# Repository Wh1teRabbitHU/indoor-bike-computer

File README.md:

# indoor-bike-computer

- [indoor-bike-computer](#indoor-bike-computer)
	- [Description](#description)
	- [Sensors](#sensors)
		- [Candelance sensor](#candelance-sensor)
		- [Difficulty sensor](#difficulty-sensor)
	- [Firmware](#firmware)
	- [Images](#images)
		- [Computer 3D render, Front](#computer-3d-render-front)
		- [Computer 3D render, Back](#computer-3d-render-back)

## Description

It's a custom computer for indoor bikes to measure cadence, speed and power, store sessions, visualise ongoing statistics and replace non chargeable solutions. This project is created for the [Joroto X2 Pro](https://jorotofitness.com/products/joroto-x2pro-bluetooth-stationary-exercise-bike) indoor bike, but can be used with any other, similarly operating bikes as well!

The sensors connect to the unit the following way:

There are 2 sensor headers on the computer, one for the Candelance sensor and the other to measure the manual difficulty adjustment knob.

## Sensors

### Candelance sensor

You need to connect the following 2 pins:

- Revolution signal: This signal sends a pulse whenever the bike's crank is aligned with the sensor. The signal is triggered once every revolution and the speed is calculated based on the time difference between two pulse. For precise distance measurement, you can change the default values of the bike in the settings.
- GND: This is the shared GND line

### Difficulty sensor

You need to connect the following 3 pins:

- +3V3: This powers the sensor on the bike
- Difficulty signal: This comes from the knob, and depending on the current difficulty level, it provides a voltage between GND and +3V3 volt. (it's not a linear value and there is a starting and ending voltage level) This can be calibrated in the settings on the computer for a precise measurement.
- GND: This is the shared GND line

## Firmware

I'm using [LVGL](https://lvgl.io/) an open source embedded graphics library, to handle the UI elements for the computer. The drivers for the various chips and the bike are custom made and can be located under the `Firmware/STM32F446/Core/Inc/Drivers` and `Firmware/STM32F446/Core/Src/Drivers` folders.

List of drivers:

- ER_TFT035: Display driver. [Details](https://www.buydisplay.com/serial-spi-3-5-inch-tft-lcd-module-in-320x480-optl-touchscreen-ili9488)
- MCP3421: ADC chip from MicroChip. [Details](https://www.microchip.com/en-us/product/mcp3421)
- SD card: SD card middleware on top of the FatFS implementation, to make handling file read and write simpler

## Images

### Computer 3D render, Front

### Computer 3D render, Back

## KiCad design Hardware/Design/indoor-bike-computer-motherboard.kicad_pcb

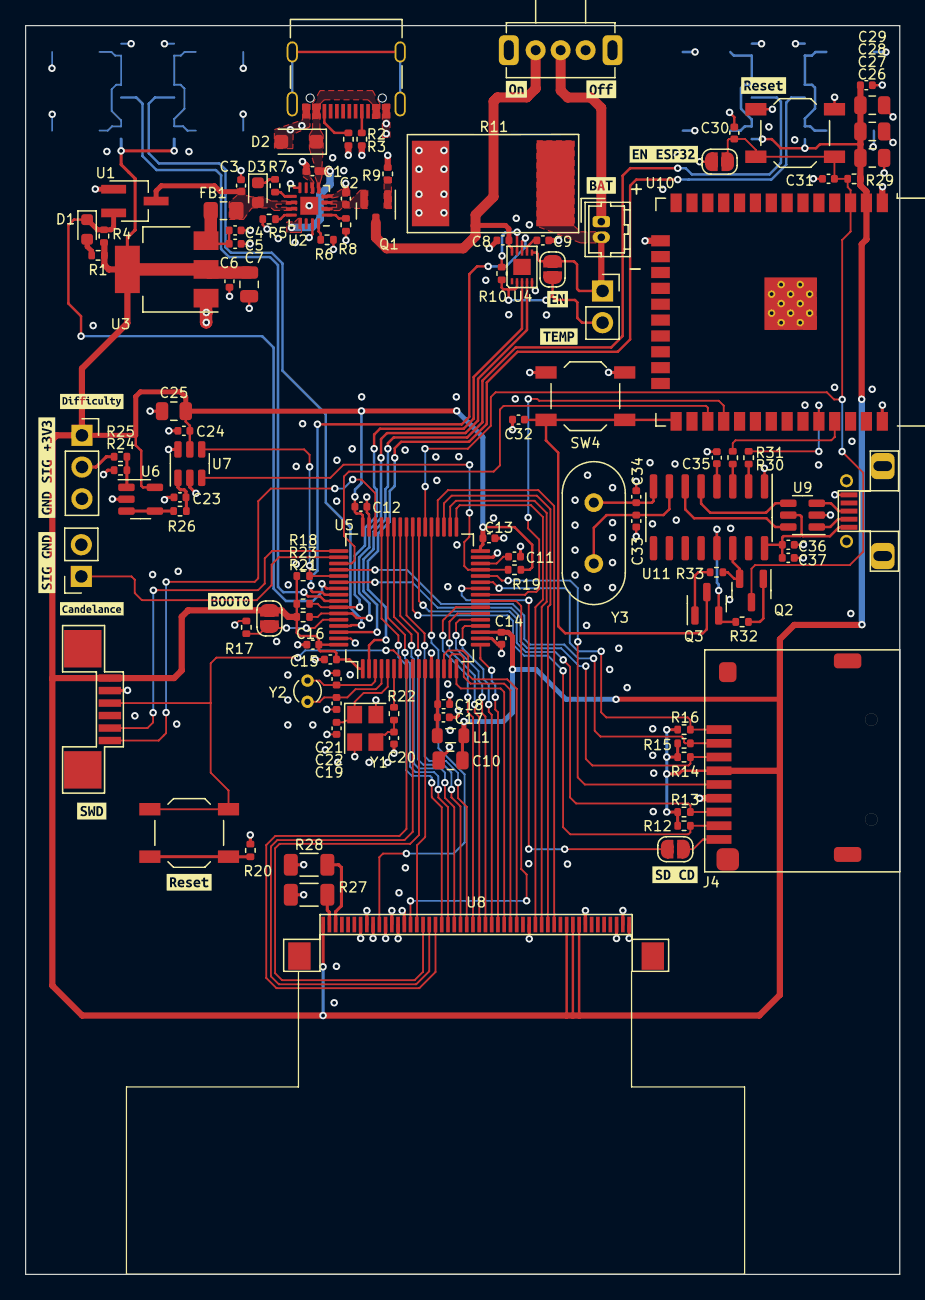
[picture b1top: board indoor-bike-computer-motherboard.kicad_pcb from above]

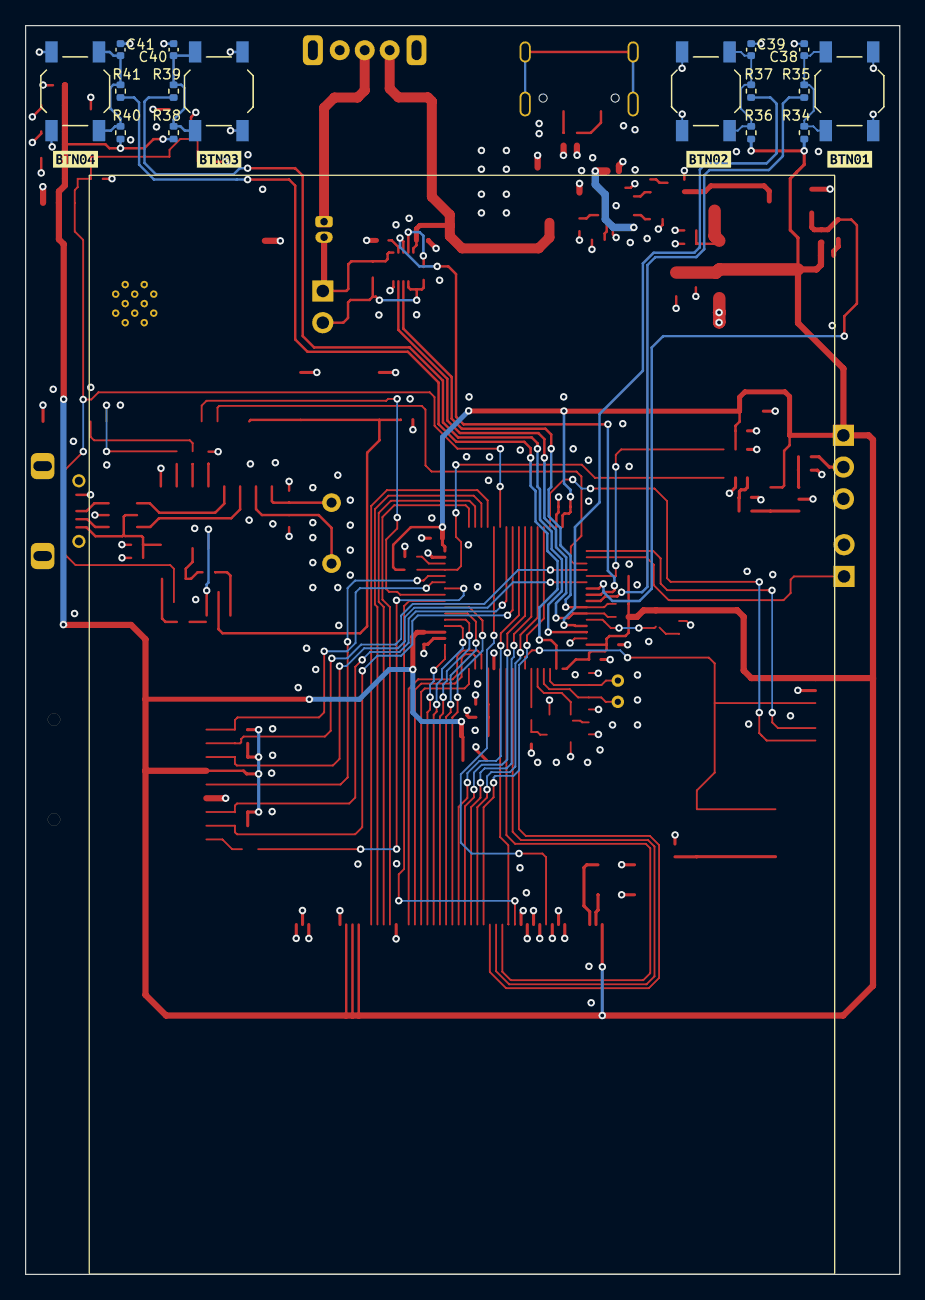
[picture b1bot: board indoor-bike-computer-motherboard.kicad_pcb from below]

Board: 4 copper layers, 70.0 x 100.0 mm, 143 parts (20 on the bottom side), 105 nets.

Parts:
C1, C9, C17, C23: 1uF; C_0402_1005Metric
C2, C3, C4, C11, C36: 4.7uF; C_0402_1005Metric
C5, C6, C8, C12, C13, C14, C15, C16, C18, C24, C29, C30, C31, C32, C35, C37, C38, C39, C40, C41: 0.1uF; C_0402_1005Metric
C7, C10, C25: 10uF; C_0805_2012Metric
C19, C20: 26pF; C_0402_1005Metric
C21, C22: 12pF; C_0402_1005Metric
C26, C27, C28: 22uF; C_0805_2012Metric
C33, C34: 15pF; C_0402_1005Metric
D1: Power Alert; LED_0603_1608Metric
D2: SMF6.0A; D_SOD-123F
D3: Charging; LED_0603_1608Metric
FB1: FerriteBead_Small; L_0805_2012Metric_Pad1.15x1.40mm_HandSolder
J1: USB_C_Receptacle_PowerOnly_6P; USB_C_Receptacle U262-161N-4BVC11
J2: Battery Terminal; Hirose_DF13-02P-1.25DSA_1x02_P1.25mm_Vertical
J3: THRM Socket; PinSocket_1x02_P2.54mm_Vertical
J4: Micro_SD_Card; MicroSD-TF-015
J5: SWD; AFA07-S06FCA-00
J6: Difficulty Header; PinSocket_1x03_P2.54mm_Vertical
J7: Candelance Header; PinSocket_1x02_P2.54mm_Vertical
J8: ESP32 Programmer; Micro_USB_B_Female
JP1: AIN_JMP; SolderJumper-2_P1.3mm_Open_RoundedPad1.0x1.5mm
JP2: SD_CD JP; SolderJumper-2_P1.3mm_Open_RoundedPad1.0x1.5mm
JP3: Jumper_2_Open; SolderJumper-2_P1.3mm_Open_RoundedPad1.0x1.5mm
JP4: EN_ESP32; SolderJumper-2_P1.3mm_Open_RoundedPad1.0x1.5mm
L1: 39nH; L_0805_2012Metric
Q1: AO3401A; SOT-23
Q2, Q3: BC849; SOT-23
R1: 1.5k; R_0402_1005Metric
R2, R3: 5.1kΩ; R_0402_1005Metric
R4: 100k; R_0402_1005Metric
R5: 1K1Ω; R_0402_1005Metric
R6: 590Ω; R_0402_1005Metric
R7, R35, R37, R39, R41: 1K; R_0402_1005Metric
R8, R9, R34, R36, R38, R40: 10K; R_0402_1005Metric
R10, R12, R13, R14, R15, R16, R17, R20, R24, R25, R29, R32, R33: 10k; R_0402_1005Metric
R11: 10mΩ; Resistor_SMD_4527
R18, R19, R21, R23: 2k2; R_0402_1005Metric
R22, R30, R31: 100; R_0402_1005Metric
R26: 220; R_0402_1005Metric
R27, R28: 10Ω; R_1206_3216Metric
SW1: Enable; Toggle-Switch-SK12D07VG4
SW2: Reset Button; SW_SPST_TL3342
SW3: Reset BTN; SW_SPST_TL3342
SW4: Flash BTN; SW_SPST_TL3342
SW5, SW6, SW7, SW8: Button_01; SW_SPST_TL3342
U1: APX803L05-36SA-7; SOT-23W_Handsoldering
U2: BQ24078RGTR; VQFN-16-1EP_3x3mm_P0.5mm_EP1.45x1.45mm
U3: LDL1117S33R; SOT-223-3_TabPin2
U4: MAX17055ETB+T; TDFN-EP-10-2.0x2.5
U5: STM32F446RETx; LQFP-64_10x10mm_P0.5mm
U6: LMV321; SOT-23-5
U7: MCP3421A0T-ECH; SOT-23-6
U8: ER-TFT035-6
U9: USBLC6-2SC6; SOT-23-6
U10: ESP32-WROOM-32
U11: CH340G; SOIC-16_3.9x9.9mm_P1.27mm
Y1: 8MHz; Crystal_SMD_Abracon_ABM8G-4Pin_3.2x2.5mm
Y2: 32768Hz; Crystal_Round_D1.5mm_Vertical
Y3: 12MHz; Crystal_HC49-4H_Vertical
kibuzzard-66A143C0: G***; kibuzzard-66A143C0
kibuzzard-66A143CA: G***; kibuzzard-66A143CA
kibuzzard-66A145A5: G***; kibuzzard-66A145A5
kibuzzard-66A145C4: G***; kibuzzard-66A145C4
kibuzzard-66A145EF: G***; kibuzzard-66A145EF
kibuzzard-66A146E2: G***; kibuzzard-66A146E2
kibuzzard-66A1432C: G***; kibuzzard-66A1432C
kibuzzard-66A1459C: G***; kibuzzard-66A1459C
kibuzzard-66A1487C: G***; kibuzzard-66A1487C
kibuzzard-66A1489C: G***; kibuzzard-66A1489C
kibuzzard-66A14353: G***; kibuzzard-66A14353
kibuzzard-66A14385: G***; kibuzzard-66A14385
kibuzzard-66A14397: G***; kibuzzard-66A14397
kibuzzard-66A14462: G***; kibuzzard-66A14462
kibuzzard-66A14469: G***; kibuzzard-66A14469
kibuzzard-66A14601: G***; kibuzzard-66A14601
kibuzzard-66A14776: G***; kibuzzard-66A14776
kibuzzard-66A14875: G***; kibuzzard-66A14875
kibuzzard-66A14886: G***; kibuzzard-66A14886

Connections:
+3.3VA: C17.1, C18.1, L1.1, U5.13 (VDDA)
/ESP32_MCU/+3V3: C6.1, C7.1, C10.1, C12.1, C13.1, C14.1, C15.1, C16.1, C24.2, C25.1, C26.1, C27.1, C28.1, C29.1, J4.4 (VDD), J5.1, J6.1, JP3.2 (B), L1.2, R1.1, R4.1, R12.2, R13.2, R14.2, R15.2, R16.2, R18.1, R19.1, R21.1, R23.1, R29.2, R34.1, R36.1, R38.1, R40.1, U3.2 (OUT), U5.1 (VBAT), U5.19 (VDD), U5.32 (VDD), U5.48 (VDD), U5.64 (VDD), U6.5 (V+), U7.5 (Vdd), U8.1 (LEDA), U8.40 (VDDI), U8.41 (VDDI), U8.42 (VCI), U10.2 (VDD)
/ESP32_MCU/ESP32_5V: C36.1, C37.1, J8.1 (VBUS), U9.5 (VBUS), U11.16 (VCC)
/ESP32_MCU/GND: C1.2, C2.2, C3.2, C4.2, C5.2, C6.2, C7.2, C8.2, C9.2, C10.2, C11.2, C12.2, C13.2, C14.2, C15.2, C16.2, C17.2, C18.2, C19.1, C20.2, C21.2, C22.2, C23.2, C24.1, C25.2, C26.2, C27.2, C28.2, C29.2, C30.2, C31.2, C32.2, C33.2, C34.2, C35.2, C36.2, C37.2, C38.2, C39.2, C40.2, C41.2, D2.2 (A2), J1.A1, J1.A12 (GND), J1.B1, J1.B12 (GND), J4.6 (VSS), J5.2, J6.3, J7.2, J8.5 (GND), JP4.1 (A), R2.2, R3.2, R5.1, R6.1, R8.2, R9.2, R11.2, R17.2, R20.2, R25.1, R27.2, R28.2, SW3.2, SW4.2, SW5.1, SW6.1, SW7.1, SW8.1, U1.1 (GND), U2.4 (!CE), U2.6 (EN1), U2.8 (VSS), U2.15 (SYSOFF), U2.17 (PAD), U3.1 (GND), U4.5 (CSN), U5.12 (VSSA), U5.18 (VSS), U5.31 (VSS), U5.47 (VSS), U5.63 (VSS), U6.2 (V-), U7.2 (Vss), U7.6 (Vin-), U8.7 (IM0), U8.8 (IM1), U8.9 (IM2), U8.11 (VSYNC), U8.12 (HSYNC), U8.13 (DOTCLK), U8.14 (DE), U8.34 (SDA), U8.43 (GND), U8.48 (GND), U8.49 (GND), U8.50 (GND), U9.2 (GND), U10.1 (GND), U10.15 (GND), U10.38 (GND), U10.39 (GND), U11.1 (GND), Y1.2, Y1.4
/ESP32_MCU/IO0: C32.1, Q3.3 (C), SW4.1, U10.25 (IO0)
/ESP32_MCU/RXD0: R30.1, U10.34 (RXD0/IO3)
/ESP32_MCU/TXD0: R31.1, U10.35 (TXD0/IO1)
/ESP32_MCU/USB_D+: U9.4 (I/O2), U11.5 (UD+)
/ESP32_MCU/USB_D-: U9.6 (I/O1), U11.6 (UD-)
/ESP32_MCU/USB_D_IN+: J8.3 (D+), U9.3 (I/O2)
/ESP32_MCU/USB_D_IN-: J8.2 (D-), U9.1 (I/O1)
/Power Input/BAT+: C2.1, Q1.2 (S), U2.2 (BAT), U2.3 (BAT)
/Power Input/BAT_IN+: C8.1, Q1.3 (D), SW1.3 (C), U4.10 (BATT)
/Power Input/BAT_IN-: J2.2, J3.1, JP1.1 (A), R11.1, U4.6 (CSP)
/Power Input/PWR_OUT: C3.1, D3.2 (A), FB1.1, U1.3 (VCC), U2.10 (OUT), U2.11 (OUT)
/Power Input/VBUS: C1.1, D2.1 (A1), J1.A4, J1.A9 (VBUS), J1.B4, J1.B9 (VBUS), U2.5 (EN2), U2.13 (IN)
ADC_SCL: R19.2, U5.29 (PB10), U7.3 (SCL)
ADC_SDA: R18.2, U5.53 (PC12), U7.4 (SDA)
BOOT0: JP3.1 (A), R17.1, U5.60 (BOOT0)
DIFFICULTY_SIGNAL: J6.2, R24.2
DISPLAY_CS: U5.36 (PB15), U8.38 (CSX)
DISPLAY_D00: U5.14 (PA0), U8.32 (DB00)
DISPLAY_D01: U5.15 (PA1), U8.31 (DB01)
DISPLAY_D02: U5.16 (PA2), U8.30 (DB02)
DISPLAY_D03: U5.17 (PA3), U8.29 (DB03)
DISPLAY_D04: U5.20 (PA4), U8.28 (DB04)
DISPLAY_D05: U5.21 (PA5), U8.27 (DB05)
DISPLAY_D06: U5.22 (PA6), U8.26 (DB06)
DISPLAY_D07: U5.23 (PA7), U8.25 (DB07)
DISPLAY_D08: U5.41 (PA8), U8.24 (DB08)
DISPLAY_D09: U5.42 (PA9), U8.23 (DB09)
DISPLAY_D10: U5.43 (PA10), U8.22 (DB10)
DISPLAY_D11: U5.44 (PA11), U8.21 (DB11)
DISPLAY_D12: U5.45 (PA12), U8.20 (DB12)
DISPLAY_D13: U5.8 (PC0), U8.19 (DB13)
DISPLAY_D14: U5.9 (PC1), U8.18 (DB14)
DISPLAY_D15: U5.10 (PC2), U8.17 (DB15)
DISPLAY_D16: U5.11 (PC3), U8.16 (DB16)
DISPLAY_D17: U5.24 (PC4), U8.15 (DB17)
DISPLAY_DC: U5.35 (PB14), U8.37 (D/CX)
DISPLAY_RD: U5.33 (PB12), U8.35 (RD)
DISPLAY_RESET: U5.37 (PC6), U8.10 (RESET)
DISPLAY_WR: U5.34 (PB13), U8.36 (WRX/SCL)
NRST: J5.3, SW2.1, U5.7 (NRST)
unnamed: C20.1, R22.1, Y1.3
unnamed: C38.1, R34.2, R35.1, SW5.2
unnamed: C39.1, R36.2, R37.1, SW6.2
unnamed: C40.1, R38.2, R39.1, SW7.2
unnamed: C41.1, R40.2, R41.1, SW8.2
unnamed: D1.2 (A), R1.2
unnamed: D3.1 (K), R7.1
unnamed: J1.A5 (CC1), R3.1
unnamed: J1.B5 (CC2), R2.1
unnamed: J2.1, SW1.2 (B)
unnamed: J3.2, JP1.2 (B), R10.1, U4.2 (AIN)
unnamed: J4.9 (SHIELD), JP2.2 (B)
unnamed: Q1.1 (G), R9.1
unnamed: Q2.1 (B), R32.1
unnamed: Q2.2 (E), R33.2, U11.14 (~RTS)
unnamed: Q3.1 (B), R33.1
unnamed: Q3.2 (E), R32.2, U11.13 (~DTR)
unnamed: R20.1, SW2.2
unnamed: R27.1, U8.2 (LEDK)
unnamed: R28.1, U8.3 (LEDK)
unnamed: R7.2, U2.9 (!CHG)
unnamed: R5.2, U2.12 (ILIM)
unnamed: R6.2, U2.16 (ISET)
unnamed: R8.1, U2.1 (TS)
unnamed: C4.1, C5.1, FB1.2, U3.3 (VIN)
unnamed: C9.1, U4.7 (REG)
unnamed: R10.2, U4.9 (THRM)
unnamed: C11.1, U5.30 (VCAP_1)
unnamed: R24.1, R25.2, U6.1 (+)
unnamed: R26.1, U6.3 (-), U6.4
unnamed: C23.1, R26.2, U7.1 (Vin+)
unnamed: R31.2, U11.3 (RXD)
unnamed: R30.2, U11.2 (TXD)
unnamed: C35.1, U11.4 (V3)
unnamed: C33.1, U11.7 (XI), Y3.1
unnamed: C34.1, U11.8 (XO), Y3.2
OSC_IN: C19.2, U5.5 (PH0), Y1.1
OSC_OUT: R22.2, U5.6 (PH1)
PA13: J5.6, U5.46 (PA13)
PA14: J5.5, U5.49 (PA14)
PA15: J7.1, U5.50 (PA15)
PB0: JP2.1 (A), U5.26 (PB0)
PB1: J4.1 (DAT2), R16.1, U5.27 (PB1)
PB2: J4.5 (CLK), U5.28 (PB2)
PB3: D1.1 (K), R4.2, U1.2 (!RESET), U5.55 (PB3)
PB4: U4.8 (ALERT), U5.56 (PB4)
PB5: R35.2, U5.57 (PB5)
PB6: R23.2, U4.3 (SCL), U5.58 (PB6)
PB7: R21.2, U4.4 (SDA), U5.59 (PB7)
PB8: R37.2, U5.61 (PB8)
PB9: R39.2, U5.62 (PB9)
PC5: U5.25 (PC5), U10.28 (IO17)
PC7: C30.1, C31.1, JP4.2 (B), Q2.3 (C), R29.1, SW3.1, U5.38 (PC7), U10.3 (EN)
PC8: J4.7 (DAT0), R13.1, U5.39 (PC8)
PC9: J4.8 (DAT1), R12.1, U5.40 (PC9)
PC10: U5.51 (PC10), U10.27 (IO16)
PC11: J4.2 (DAT3/CD), R15.1, U5.52 (PC11)
PC13: R41.2, U5.2 (PC13)
PC14: C21.1, U5.3 (PC14), Y2.1
PC15: C22.1, U5.4 (PC15), Y2.2
PD2: J4.3 (CMD), R14.1, U5.54 (PD2)

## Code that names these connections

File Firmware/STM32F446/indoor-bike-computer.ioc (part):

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Mcu.Name=STM32F446R(C-E)Tx
Mcu.Package=LQFP64
Mcu.UserName=STM32F446RETx
PA0-WKUP.GPIOParameters=GPIO_Label
PA0-WKUP.GPIO_Label=DISPLAY_D00
PA0-WKUP.Signal=GPIO_Output
PA1.GPIOParameters=GPIO_Label
PA1.GPIO_Label=DISPLAY_D01
PA1.Signal=GPIO_Output
PA10.GPIOParameters=GPIO_Label
PA10.GPIO_Label=DISPLAY_D10
PA10.Signal=GPIO_Output
PA11.GPIOParameters=GPIO_Label
PA11.GPIO_Label=DISPLAY_D11
PA11.Signal=GPIO_Output
PA12.GPIOParameters=GPIO_Label
PA12.GPIO_Label=DISPLAY_D12
PA12.Signal=GPIO_Output
PA13.Mode=Serial_Wire
PA13.Signal=SYS_JTMS-SWDIO
PA14.Mode=Serial_Wire
PA14.Signal=SYS_JTCK-SWCLK
PA15.GPIOParameters=GPIO_PuPd,GPIO_Label,GPIO_ModeDefaultEXTI
PA15.GPIO_Label=REVOLUTION_SIGNAL
PA15.GPIO_ModeDefaultEXTI=GPIO_MODE_IT_FALLING
PA15.GPIO_PuPd=GPIO_PULLUP
PA15.Signal=GPXTI15
PA2.GPIOParameters=GPIO_Label
PA2.GPIO_Label=DISPLAY_D02
PA2.Signal=GPIO_Output
PA3.GPIOParameters=GPIO_Label
PA3.GPIO_Label=DISPLAY_D03
PA3.Signal=GPIO_Output
PA4.GPIOParameters=GPIO_Label
PA4.GPIO_Label=DISPLAY_D04
PA4.Signal=GPIO_Output
PA5.GPIOParameters=GPIO_Label
PA5.GPIO_Label=DISPLAY_D05
PA5.Signal=GPIO_Output
PA6.GPIOParameters=GPIO_Label
PA6.GPIO_Label=DISPLAY_D06
PA6.Signal=GPIO_Output
PA7.GPIOParameters=GPIO_Label
PA7.GPIO_Label=DISPLAY_D07
PA7.Signal=GPIO_Output
PA8.GPIOParameters=GPIO_Label
PA8.GPIO_Label=DISPLAY_D08
PA8.Signal=GPIO_Output
PA9.GPIOParameters=GPIO_Label
PA9.GPIO_Label=DISPLAY_D09
PA9.Signal=GPIO_Output
PB0.GPIOParameters=GPIO_Label
PB0.GPIO_Label=SDIO_CD
PB0.Signal=GPIO_Input
PB10.Mode=I2C
PB10.Signal=I2C2_SCL
PB12.GPIOParameters=GPIO_Label
PB12.GPIO_Label=DISPLAY_RD
PB12.Signal=GPIO_Output
PB13.GPIOParameters=GPIO_Label
PB13.GPIO_Label=DISPLAY_WR
PB13.Signal=GPIO_Output
PB14.GPIOParameters=GPIO_Label
PB14.GPIO_Label=DISPLAY_DC
PB14.Signal=GPIO_Output
PB15.GPIOParameters=GPIO_Label
PB15.GPIO_Label=DISPLAY_CS
PB15.Signal=GPIO_Output
PB2.GPIOParameters=GPIO_Speed_High_Default
PB2.GPIO_Speed_High_Default=GPIO_SPEED_FREQ_MEDIUM
PB2.Mode=SD_1_bit
PB2.Signal=SDIO_CK
PB3.GPIOParameters=GPIO_Label
PB3.GPIO_Label=POWER_ALERT
PB3.Signal=GPIO_Input
PB4.GPIOParameters=GPIO_Label
PB4.GPIO_Label=GAUGE_ALERT
PB4.Signal=GPIO_Output
PB5.GPIOParameters=GPIO_Label
PB5.GPIO_Label=USER_BTN_1
PB5.Signal=GPXTI5
PB6.Mode=I2C
PB6.Signal=I2C1_SCL
PB7.Mode=I2C
PB7.Signal=I2C1_SDA
PB8.GPIOParameters=GPIO_Label
PB8.GPIO_Label=USER_BTN_2
PB8.Signal=GPXTI8
PB9.GPIOParameters=GPIO_Label
PB9.GPIO_Label=USER_BTN_3
PB9.Signal=GPXTI9
PC0.GPIOParameters=GPIO_Label
PC0.GPIO_Label=DISPLAY_D13
PC0.Signal=GPIO_Output
PC1.GPIOParameters=GPIO_Label
PC1.GPIO_Label=DISPLAY_D14
PC1.Signal=GPIO_Output
PC10.Mode=Asynchronous
PC10.Signal=USART3_TX
PC12.Mode=I2C
PC12.Signal=I2C2_SDA
PC13.GPIOParameters=GPIO_Label
PC13.GPIO_Label=USER_BTN_4
PC13.Signal=GPXTI13
PC14-OSC32_IN.Mode=LSE-External-Oscillator
PC14-OSC32_IN.Signal=RCC_OSC32_IN
PC15-OSC32_OUT.Mode=LSE-External-Oscillator
PC15-OSC32_OUT.Signal=RCC_OSC32_OUT
PC2.GPIOParameters=GPIO_Label
PC2.GPIO_Label=DISPLAY_D15
PC2.Signal=GPIO_Output
PC3.GPIOParameters=GPIO_Label
PC3.GPIO_Label=DISPLAY_D16
PC3.Signal=GPIO_Output
PC4.GPIOParameters=GPIO_Label
PC4.GPIO_Label=DISPLAY_D17
PC4.Signal=GPIO_Output
PC5.Mode=Asynchronous
PC5.Signal=USART3_RX
PC6.GPIOParameters=GPIO_Label
PC6.GPIO_Label=DISPLAY_RESET
PC6.Signal=GPIO_Output
PC7.GPIOParameters=PinState,GPIO_PuPd,GPIO_Label,GPIO_ModeDefaultOutputPP
PC7.GPIO_Label=ESP32_EN
PC7.GPIO_ModeDefaultOutputPP=GPIO_MODE_OUTPUT_OD
PC7.GPIO_PuPd=GPIO_NOPULL
PC7.PinState=GPIO_PIN_SET
PC7.Signal=GPIO_Output
PC8.GPIOParameters=GPIO_PuPd,GPIO_Speed_High_Default
PC8.GPIO_PuPd=GPIO_NOPULL
PC8.GPIO_Speed_High_Default=GPIO_SPEED_FREQ_MEDIUM
PC8.Mode=SD_1_bit
PC8.Signal=SDIO_D0
PD2.GPIOParameters=GPIO_PuPd,GPIO_Speed_High_Default
PD2.GPIO_PuPd=GPIO_NOPULL
PD2.GPIO_Speed_High_Default=GPIO_SPEED_FREQ_MEDIUM
PD2.Mode=SD_1_bit
PD2.Signal=SDIO_CMD
PH0-OSC_IN.Mode=HSE-External-Oscillator
PH0-OSC_IN.Signal=RCC_OSC_IN
PH1-OSC_OUT.Mode=HSE-External-Oscillator
PH1-OSC_OUT.Signal=RCC_OSC_OUT
RCC.HSE_VALUE=8000000
RCC.SYSCLKFreq_VALUE=180000000
RCC.SYSCLKSource=RCC_SYSCLKSOURCE_PLLCLK
board=custom

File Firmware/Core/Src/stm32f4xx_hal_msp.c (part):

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
    __HAL_RCC_GPIOB_CLK_ENABLE();
    /**I2C1 GPIO Configuration
    PB6     ------> I2C1_SCL
    PB7     ------> I2C1_SDA
    */
    GPIO_InitStruct.Pin = GPIO_PIN_6|GPIO_PIN_7;
    GPIO_InitStruct.Mode = GPIO_MODE_AF_OD;
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    __HAL_RCC_GPIOB_CLK_ENABLE();
    __HAL_RCC_GPIOC_CLK_ENABLE();
    /**I2C2 GPIO Configuration
    PB10     ------> I2C2_SCL
    PC12     ------> I2C2_SDA
    */
    GPIO_InitStruct.Pin = GPIO_PIN_10;
    GPIO_InitStruct.Mode = GPIO_MODE_AF_OD;
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    __HAL_RCC_I2C1_CLK_DISABLE();

    /**I2C1 GPIO Configuration
    PB6     ------> I2C1_SCL
    PB7     ------> I2C1_SDA
    */
    HAL_GPIO_DeInit(GPIOB, GPIO_PIN_6);

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    __HAL_RCC_I2C2_CLK_DISABLE();

    /**I2C2 GPIO Configuration
    PB10     ------> I2C2_SCL
    PC12     ------> I2C2_SDA
    */
    HAL_GPIO_DeInit(GPIOB, GPIO_PIN_10);

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    __HAL_RCC_GPIOC_CLK_ENABLE();
    __HAL_RCC_GPIOD_CLK_ENABLE();
    /**SDIO GPIO Configuration
    PB1     ------> SDIO_D2
    PB2     ------> SDIO_CK
    PC8     ------> SDIO_D0
    PC9     ------> SDIO_D1
    PC11     ------> SDIO_D3
    PD2     ------> SDIO_CMD
    */
    GPIO_InitStruct.Pin = GPIO_PIN_1|GPIO_PIN_2;
    GPIO_InitStruct.Mode = GPIO_MODE_AF_PP;
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    __HAL_RCC_SDIO_CLK_DISABLE();

    /**SDIO GPIO Configuration
    PB1     ------> SDIO_D2
    PB2     ------> SDIO_CK
    PC8     ------> SDIO_D0
    PC9     ------> SDIO_D1
    PC11     ------> SDIO_D3
    PD2     ------> SDIO_CMD
    */
    HAL_GPIO_DeInit(GPIOB, GPIO_PIN_1|GPIO_PIN_2);

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
    __HAL_RCC_GPIOC_CLK_ENABLE();
    /**USART3 GPIO Configuration
    PC5     ------> USART3_RX
    PC10     ------> USART3_TX
    */
    GPIO_InitStruct.Pin = GPIO_PIN_5|GPIO_PIN_10;
    GPIO_InitStruct.Mode = GPIO_MODE_AF_PP;
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    __HAL_RCC_USART3_CLK_DISABLE();

    /**USART3 GPIO Configuration
    PC5     ------> USART3_RX
    PC10     ------> USART3_TX
    */
    HAL_GPIO_DeInit(GPIOC, GPIO_PIN_5|GPIO_PIN_10);

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
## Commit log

2024-02-26 Init STM32 project
2024-02-26 basic 18 bit display driver
2024-02-26 advanced 18 bit display driver
2024-02-26 Rotating the screen 180 degrees (changing 0x36 register)
2024-02-28 Adding MCP3421 library
2024-02-28 Reading difficulty sensor
2024-02-28 Removing unnecessary multiplication
2024-02-28 Moving the STM32 firmware under a subfolder
2024-02-29 Add ESP32 base project
2024-02-29 Enable interrupts
2024-02-29 Showing RPM
2024-02-29 Added general timer (to read difficulty value later)
2024-03-03 Add LVGL library to the project
2024-03-03 Refactor GUI component
2024-03-03 Making the GUI library thread safe
2024-03-03 Fixing the font
2024-03-04 Small folder structure refactor
2024-03-04 Refactor and add generic box element
2024-03-04 Basic boxes on the main screen
2024-03-06 Adding the chart to the screen
2024-03-06 Small adjustment on the chart
2024-03-06 Removing unused variable
2024-03-06 Add timer element
2024-03-06 Working timer
2024-03-06 Proper chart tick secondly
2024-03-25 Add tab view components and handle button press
2024-03-26 Small changes
2024-03-26 Refactor main screen component
2024-03-27 Refactor code
2024-03-27 Further refactor, splitting the code into components
2024-03-27 Moving implementation to tab view component
2024-03-27 Naming simplification
2024-03-29 Further refactor
2024-03-29 Implementing further controls and optimising code generation
2024-03-31 Speed up the display driver
2024-03-31 Add control live and handle navigating it
2024-04-06 Refactor state handling
2024-04-06 Rename state handlers and add new state
2024-04-06 Handle stoptimer properly
2024-08-04 Adding toggle and change text
2024-08-04 Adding SD Card support
2024-08-11 Refactoring the SD card driver, adding new functions and preparing the data interface
2024-08-12 Adding folder reader method, can be used to step through the tree
2024-09-16 Recursive directory creation; create run
2024-09-16 Directory statistics; count the runs on the SD Card
2024-09-18 Init run function; Count measurements in a run function
2024-09-18 Read run data from SD Card
2024-09-28 Read run measurements
2024-09-28 Store run measurement
2024-09-29 Small cleanup and refactor in the data module
2024-09-30 Storing run data on SD card
2024-10-06 Small refactor
2024-10-06 Linking the history tab functions to the flow handlers
2024-10-06 Adding the loading logic to the history tab and implement a loading label
2024-10-26 Initial run details history implementation
2024-10-26 Fix load and scrolling
2024-10-29 Handle statistics and delete runs
2024-10-29 Fixing distance calculation and live control states
2024-11-01 Adding a summary box on the history tab and change format + some smaller fixes
2024-11-03 Adding proper run details selection
2024-11-03 Adding page header to the history tab
2024-11-03 Small design adjustments
2024-11-03 Fixing the loading label
2024-11-10 Add clang-format configuration to the project
2024-11-10 Adding run details modal to the history tab
2024-11-30 Making the run details buttons work and fixing the indexing issue on the history tab
2024-11-30 Fixing some bugs
2024-12-01 Refactor components and namings
2024-12-14 Changing one of the measurements into distance and fixing some bugs
2024-12-14 Making sure a new run always writes in a new folder
2024-12-14 Adding the hardware design to the repository
2024-12-14 Add readme entries
2024-12-17 Reformating files
2024-12-22 Adding main screen alert and check if the SD card is present on startup
2024-12-25 Fixing some configuration issues
2025-01-04 Adding max17055 driver, part 1
2025-01-04 Fixing the revolution measurement issues while the session is running
2025-01-04 Using timers instead of the system clock to measure elapsed time between crank revolutions
2025-01-04 Fixing the MCP3421 measurements
2025-01-12 Trying to make the MAX17055 chip work, no success
2025-01-12 Basic ESP32 config to receive UART data from the STM32
2025-01-18 Few improvements: average value calculation is now more precise, detecting when the user stops pedalling
2025-01-19 Refactor components
2025-02-16 Adding config handler and small refactor of the MCP3421 driver
2025-02-16 Fixing the SDCard_readLine and SDCard_readLines methods Adding missing config attribute parser implementation
2025-02-16 Allow SD card error handling in debug mode; reformat header
2025-02-16 Save back configuration data
2025-06-09 Sending data to the ESP32, with checksum
2025-07-13 Setting up two way DMA UART communication
2025-07-20 Refactor the UART handling in both the ESP and STM library

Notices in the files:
Firmware/Core/Src/stm32f4xx_hal_msp.c:
Copyright (c) 2024 STMicroelectronics.
All rights reserved.
This software is licensed under terms that can be found in the LICENSE file
